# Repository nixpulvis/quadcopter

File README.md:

# Quadrocopter

 * __Nathan Lilienthal__ [@nixpulvis](https://github.com/nixpulvis)
 * __Alex Johnson__ [@alexjohnson505](https://github.com/alexjohnson505)

## Index

This project is comprised of a number of components. Below is a purpose and description for each main peice.

### gel

Gel is a simple OpenGL engine, created to assist in understanding and analyzing data through 3D visualization. One such part is the 3D representation of data provided via the IMU.

### serial_monitor

Serial monitor reads data from the Arduino by wrapping the `SerialPort` class from the `serialport` gem.

The Arduino application's serial monitor is good for human reading the output, but Serial Monitor allows additional programs to read the data.

### imu_visualization

IMU_visualization reads IMU data from the Arduino over serial, and creates 3D models of the data allowing us to create a visual 3D represenation of the captured data.

### smc

This program will sit on an Arduino acting as the quadcopter's SMC. It handles reading IMU data over I2C and performing the required math to accurately determinate valid pitch, roll, and yaw values. Based on it's knowledge of the quadcopters current inertial status, the SMC will drive the motors to the correct speed required to reach the calculated pitch, roll, yaw values.

## Tasks

We are maintaining the action items for this project on [Trello](https://trello.com/b/EygHwZfX).

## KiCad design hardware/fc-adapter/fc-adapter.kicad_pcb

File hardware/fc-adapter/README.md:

# FC adapter / power board (rev A)

A 94 × 94 mm, 2-layer, 1 oz copper, 1.6 mm FR4 board that bolts rigidly to the
frame's nylon standoffs. It carries the battery connector, the 4-way ESC power
bus, the ESC signal header, and plug-in ports for the receiver, GPS + Remote ID and PM02. It holds the Lumenier LUX F765 NDAA flight controller
(38 × 38 mm, 30.5 mm M3) on standoffs with rubber grommets.

```
  [      FC       ]   <- floats on 4x M3 rubber grommets
     |  |  |  |       <- M3 standoffs, ~10 mm, 30.5 mm square
  [  this board   ]   <- bolted rigidly to the frame standoffs
  [  frame plate  ]
```

| Top | Bottom (mirrored, as seen from below) |
|---|---|
|  |  |

Schematic: [docs/schematic.svg](docs/schematic.svg).
DRC: [docs/drc.rpt](docs/drc.rpt). Schematic/board net check: [docs/netlist-check.txt](docs/netlist-check.txt).

Rev A is the first board to be fabricated. Earlier unbuilt drafts targeted the
Matek H743-WING V3 and the CoreWing F405 WING V2, which both sold out. The LUX
has no power board or current sensor, so a Holybro PM02 sits between the
battery and this board.

## Power path

```
battery -> Holybro PM02 (current + voltage sense, cable to J9) -> J1 XT60
J1 -> ESC bus pours -> M1..M4 ESC pads
                    -> P1/P2 "FC VBAT" -> FC battery pads
```

Every power pad has a + or - mark beside it.

* **VBAT_ESC** is a near full-board pour on the top layer and **GND_ESC** on the
  bottom. Exposed copper strips beside the FC area can be loaded with solder.
* The PM02 measures all the current, motors and electronics alike, because
  everything downstream of it runs through this board.
* Signal ground (the front strip) only meets GND_ESC through the FC.
* C1 and C2 (1000 µF 35 V low-ESR each) sit across the ESC bus, one on each
  side, so the board stays balanced.
* Power pads connect solidly to the pours (no thermal reliefs), so use a big
  iron for the XT60 and wire pads.

## Signals and ports

| Ref | What | Pins |
|---|---|---|
| J2 | ESC servo plugs, 3 × 4 | rows S (signal), NC (ESC BEC 5V, not connected), G; columns S1–S4 |
| J3 | FC LINK | S1, S2, S3, S4, G |
| J5 / J6 | GPS+ID socket (JST-GH 6) / its FC lead pads | RX, TX, G, 5V, SCL, SDA |
| J7 / J8 | RX (receiver) socket (JST-GH 4) / its FC lead pads | 5V, TX, RX, G |
| J9 / J10 | PM02 socket (JST-GH 6) / its FC lead pads | socket: VCC, VCC (both NC), CUR, VOLT, G, G; pads: CUR, VOLT |

The ESC plugs fit unmodified: their red wire lands on the NC row, so the four
ESC BECs never feed the FC. J3 takes a short 5-wire lead to the FC's S1–S4 and
G pads.

The LUX has only solder pads, so every device plugs into this board instead.
Each port has a row of pads for a short lead soldered once to the FC, and a
JST-GH socket for the device:

* **GPS+ID (J5/J6)** is for the BeeID Pro M10, which does GPS, compass and Remote ID from one plug. The socket follows the BeeID Pro's
  listed order (ReadyMadeRC: TX, RX, GND, 5V, SCL, SDA, from the module's
  side), so the module's stock GH cable plugs straight in; the FC lead pads are
  labelled from the FC side (RX, TX, G, 5V, SCL, SDA). Wire J6 to one FC UART
  group plus SDA/SCL (the LUX has GND, 5V, RX3, TX3, SDA, SCL side by side).
  Check the pads printed on the module against this when it arrives.
* **RX (J7/J8)** is for the ELRS receiver. Wire J8 to another UART group (the
  LUX has TX8, RX8, 5V, GND together). The receiver's lead needs a JST-GH
  plug with its RX on the TX pin and its TX on the RX pin.
* **PM02 (J9/J10)**, at the rear by the XT60, takes the PM02's sense cable.
  Its 5V is left unconnected because the LUX has its own BEC, and its ground
  is the battery negative, which is already this board's ESC bus. So J10 only
  needs two wires: CUR to the FC's Curr pad, and optionally VOLT (the FC
  already reads the battery voltage on its VBAT pads).

The front ports all read the same way, front edge to back: the device's
connector, the pad row for the lead to the FC, the pin names, then the port's
name. The ESC header is turned so its G row is at the edge and its S row
faces the FC link.

TX and RX are named from the FC's side everywhere. Keep the receiver itself
on its lead, away from the copper pours, with the antenna out in the open.

Remote ID comes from the BeeID Pro M10 on the GPS+ID socket. NewBeeDrone's
FAA declaration RID000001995 (model "BeeID", accepted) covers serials
2071F000000000000000 to 2071FZZZZZZZZZZZZZZZ, so check the module's serial
starts with 2071F.

ArduPilot (target `LumenierLUXF765-NDAA`): motors are outputs 1–4
(`SERVOn_FUNCTION` 33–36), so J3 S1–S4 go to the FC's S1–S4.

Motor numbering follows ArduPilot Quad X: M1 front-right, M2 rear-left,
M3 front-left, M4 rear-right. Each ESC pad pair has two zip-tie slots for
strain relief.

## Still to confirm

* **Which LUX UARTs** go to J6 and J8. The silkscreen groups are read off
  photos; check them against the `LumenierLUXF765-NDAA` hwdef and set
  `SERIALn_PROTOCOL` (5 for GPS, 23 for RC) and `BATT_CURR_PIN` to match.
* **Frame standoffs** are 44 × 44 mm centre to centre, M3 (measured). They
  sit just outside the FC's corners, so the frame screw heads end up under
  the FC, which clears them on its ~10 mm standoffs. The nuts or screw ends
  of the FC standoffs hang under this board, so the frame standoffs must be
  taller than those.
* **Nothing taller than about 4 mm goes under the FC.** It sits about
  10 mm up on grommets and has parts on its underside, so the 54 mm square
  under it is kept for low parts only (it's empty).
* The XT60 is rated about 30 A continuous / 60 A burst. That covers hover and
  normal flight; `MOT_BAT_CURR_MAX ≈ 70` limits the peaks.

## Working on it

The KiCad files are the source of truth once you start editing in KiCad
(7.0 or newer). The scripts bootstrapped the board and are handy while the
mechanical numbers are still moving, but `generate.py` overwrites both files:

```sh
python3 scripts/generate.py   # schematic, placement, pours, the four S tracks
python3 scripts/check.py      # fill pours, DRC + schematic/board net check
scripts/export.sh             # renders (docs/) and Gerbers (fab/)
```

Use the Python that ships with KiCad (`python3.12` on Ubuntu 24.04's KiCad 7).
`scripts/route.py` (Freerouting) is only needed if signal nets come back that
`generate.py` doesn't route itself. `export.sh` writes `fab/fc-adapter-gerbers.zip`. Rev A is ordered as bare
boards from OSH Park's standard 2-layer service (1.6 mm, 1 oz, ENIG), with the
parts hand-soldered: the XT60 (J1), C1, C2 and the three GH sockets (J5, J7,
J9) besides the headers and wires. The power pours span the whole board, so
1 oz is enough; OSH Park's 2 oz service only comes as a 0.8 mm board, too
flexible for one that carries the FC.

### Ordering with assembly (JLCPCB, not used for rev A)

`export.sh` also writes `fab/jlcpcb-bom.csv` and `fab/jlcpcb-cpl.csv`. Upload
them with the Gerber zip and pick PCB Assembly. They list only the parts
JLCPCB fits: the XT60 (J1), C1, C2 and the three GH sockets (J5, J7, J9). The rest
(the ESC and FC LINK headers, wire pads and the FC lead pad rows) is soldered
by hand. Those parts are marked with `MPN`, `LCSC` and `JLCPCB` fields, which
are set in `ASSEMBLY` in `scripts/generate.py`.

* No LCSC numbers are filled in yet. JLCPCB's order page matches the part
  number and lets you pick a stocked part.
* Check every part's rotation in JLCPCB's placement preview before paying.

Project-local parts live in `lib/` (`fc-adapter.pretty`, `fc-adapter.kicad_sym`):
wire pads for 12/14AWG leads, the 3 × 4 ESC header and the zip-tie slot.
Everything else comes from KiCad's standard libraries.

KiCad 7's command line has no ERC, so `check.py` compares every pin's net in
the schematic netlist against the matching pad on the board instead.

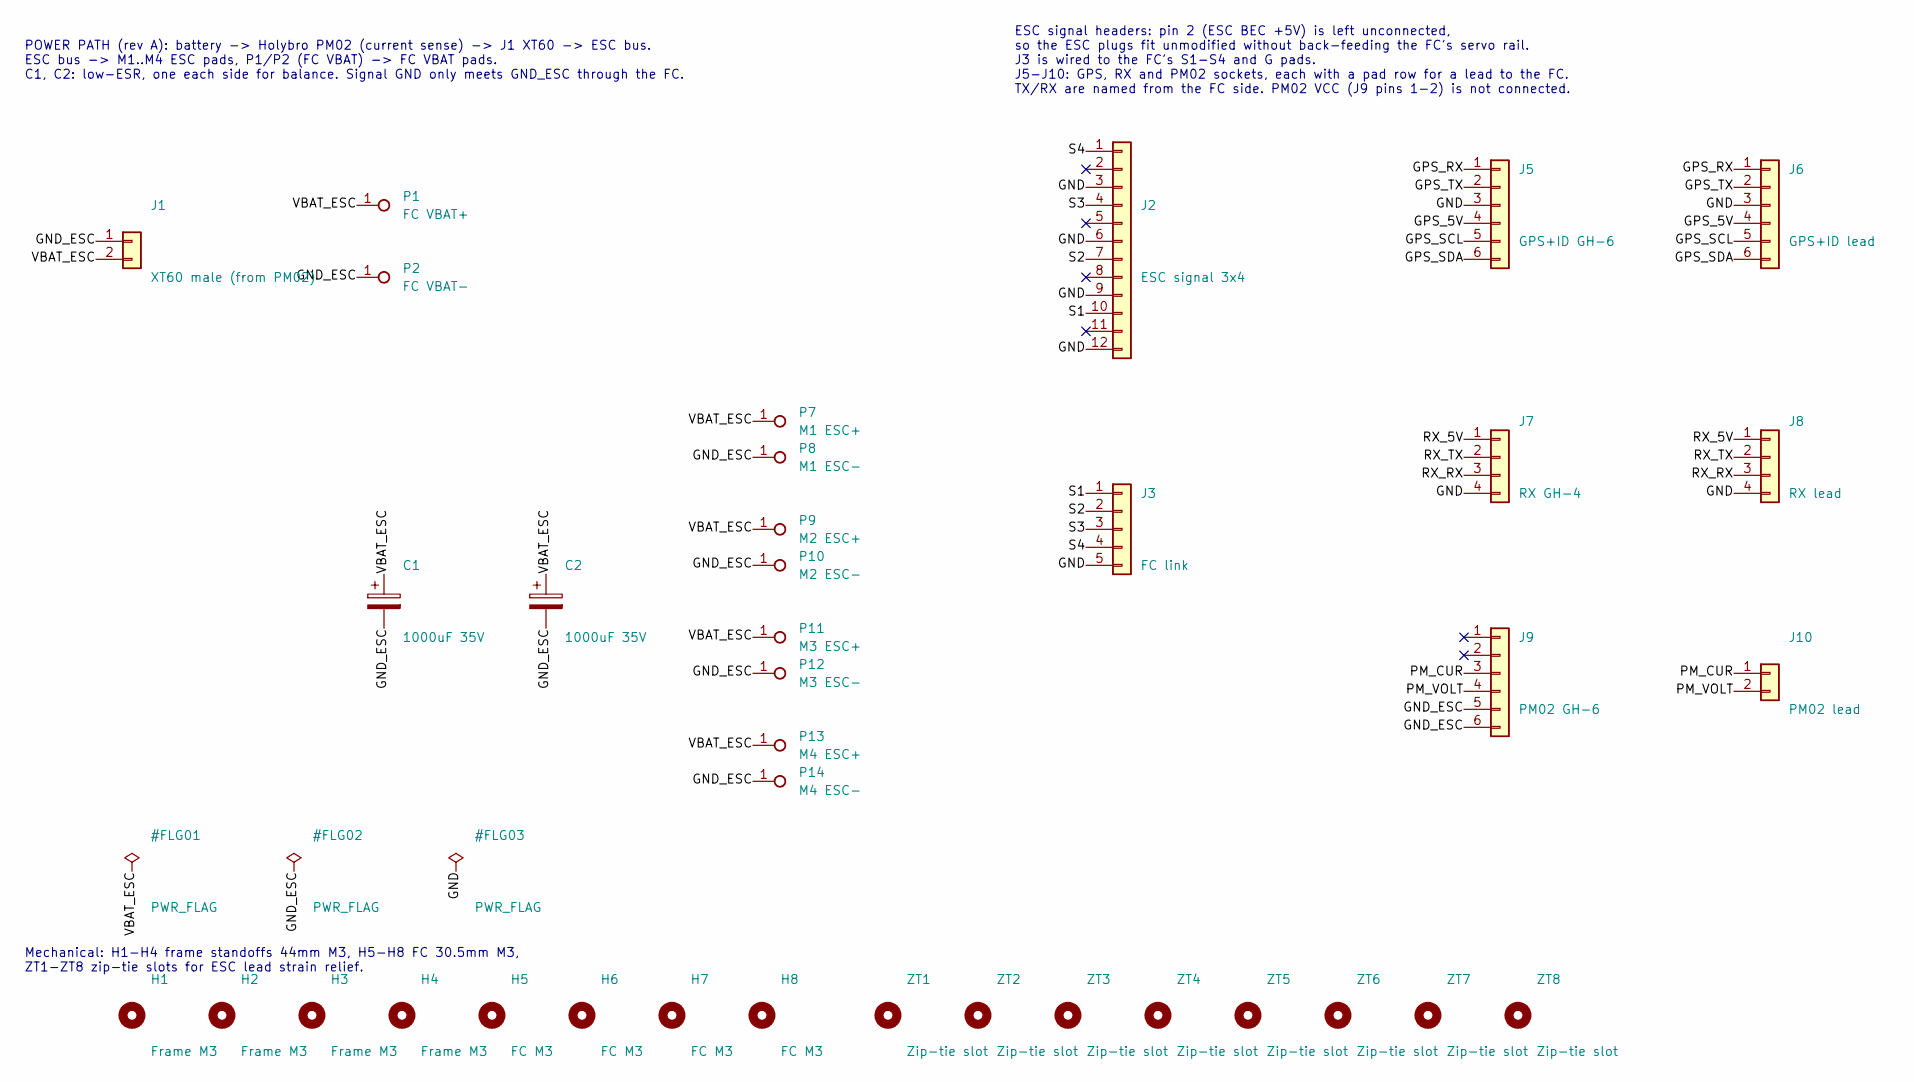
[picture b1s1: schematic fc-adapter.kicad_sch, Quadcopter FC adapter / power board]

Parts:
C1, C2: 1000uF 35V; CP_Radial_D12.5mm_P5.00mm; MPN 1000uF 35V low-ESR electrolytic, 12.5mm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; JLCPCB fit
H1, H2, H3, H4: Frame M3; MountingHole_3.2mm_M3
H5, H6, H7, H8: FC M3; MountingHole_3.2mm_M3
J1: XT60 male (from PM02); AMASS_XT60PW-M_1x02_P7.20mm_Horizontal; MPN Amass XT60PW-M; JLCPCB fit
J2: ESC signal 3x4; ESC_Header_3x04_P2.54mm
J3: FC link; PinHeader_1x05_P2.54mm_Vertical
J5: GPS+ID GH-6; JST_GH_BM06B-GHS-TBT_1x06-1MP_P1.25mm_Vertical; MPN JST BM06B-GHS-TBT; JLCPCB fit
J6: GPS+ID lead; PinHeader_1x06_P2.54mm_Vertical
J7: RX GH-4; JST_GH_BM04B-GHS-TBT_1x04-1MP_P1.25mm_Vertical; MPN JST BM04B-GHS-TBT; JLCPCB fit
J8: RX lead; PinHeader_1x04_P2.54mm_Vertical
J9: PM02 GH-6; JST_GH_BM06B-GHS-TBT_1x06-1MP_P1.25mm_Vertical; MPN JST BM06B-GHS-TBT; JLCPCB fit
J10: PM02 lead; PinHeader_1x02_P2.54mm_Vertical
P1: FC VBAT+; WirePad_14AWG
P2: FC VBAT-; WirePad_14AWG
P7: M1 ESC+; WirePad_14AWG
P8: M1 ESC-; WirePad_14AWG
P9: M2 ESC+; WirePad_14AWG
P10: M2 ESC-; WirePad_14AWG
P11: M3 ESC+; WirePad_14AWG
P12: M3 ESC-; WirePad_14AWG
P13: M4 ESC+; WirePad_14AWG
P14: M4 ESC-; WirePad_14AWG
ZT1, ZT2, ZT3, ZT4, ZT5, ZT6, ZT7, ZT8: Zip-tie slot; ZipTieSlot_1.6x4.0mm

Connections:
GND: J2.3, J2.6, J2.9, J2.12, J3.5, J5.3, J6.3, J7.4, J8.4
GND_ESC: C1.2, C2.2, J1.1, J9.5, J9.6, P2.1, P8.1, P10.1, P12.1, P14.1
GPS_5V: J5.4, J6.4
GPS_RX: J5.1, J6.1
GPS_SCL: J5.5, J6.5
GPS_SDA: J5.6, J6.6
GPS_TX: J5.2, J6.2
PM_CUR: J9.3, J10.1
PM_VOLT: J9.4, J10.2
RX_5V: J7.1, J8.1
RX_RX: J7.3, J8.3
RX_TX: J7.2, J8.2
S1: J2.10, J3.1
S2: J2.7, J3.2
S3: J2.4, J3.3
S4: J2.1, J3.4
VBAT_ESC: C1.1, C2.1, J1.2, P1.1, P7.1, P9.1, P11.1, P13.1

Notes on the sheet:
POWER PATH (rev A): battery -> Holybro PM02 (current sense) -> J1 XT60 -> ESC bus. ESC bus -> M1..M4 ESC pads, P1/P2 (FC VBAT) -> FC VBAT pads. C1, C2: low-ESR, one each side for balance. Signal GND only meets GND_ESC through the FC.
ESC signal headers: pin 2 (ESC BEC +5V) is left unconnected, so the ESC plugs fit unmodified without back-feeding the FC's servo rail. J3 is wired to the FC's S1-S4 and G pads. J5-J10: GPS, RX and PM02 sockets, each with a pad row for a lead to the FC. TX/RX are named from the FC side. PM02 VCC (J9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
Mechanical: H1-H4 frame standoffs 44mm M3, H5-H8 FC 30.5mm M3, ZT1-ZT8 zip-tie slots for ESC lead strain relief.

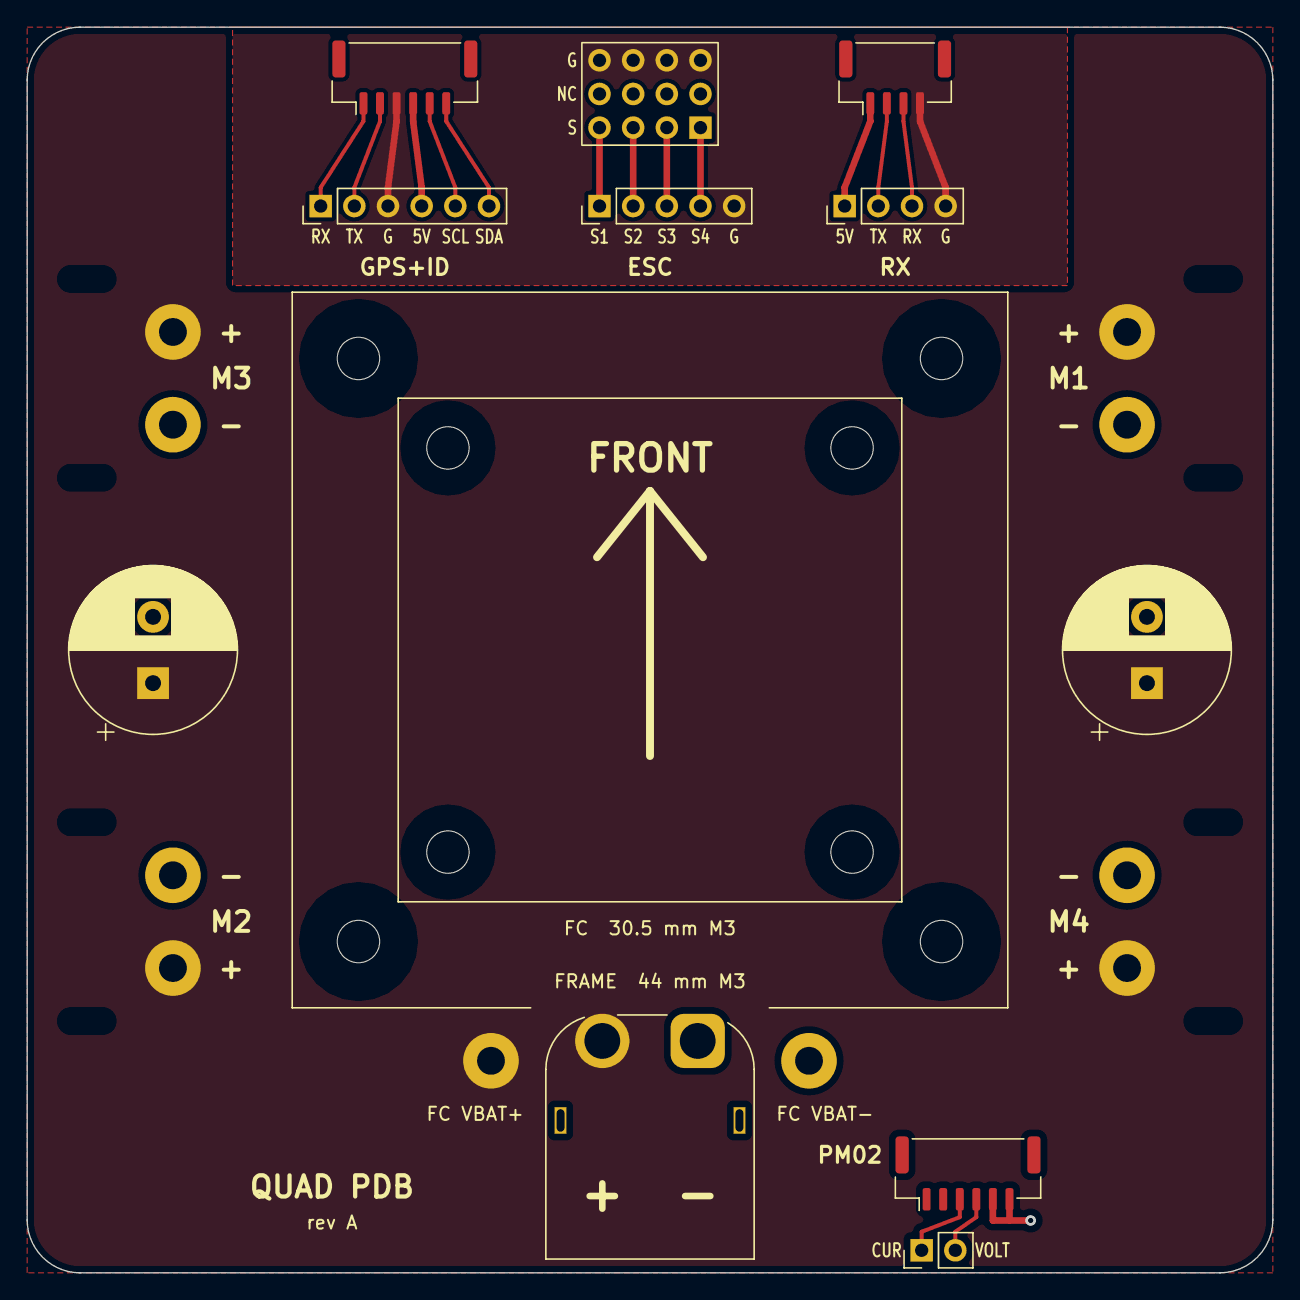
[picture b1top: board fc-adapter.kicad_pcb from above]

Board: 2 copper layers, 94.0 x 94.0 mm, 37 parts (0 on the bottom side), 17 nets.

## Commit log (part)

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2013-04-07 init
2013-04-07 add links
2013-04-07 Add more links
2013-04-09 starting parts list
2013-04-11 no checkboxes in README.md :(
2013-05-13 Adding some ESC/Motor control code.
2013-05-13 Simplification and comments.
2013-05-13 Removing parts list.
2013-05-13 Removing cruft from README.
2013-05-13 Adding some notes.
2013-05-21 Handle array of motors.
    All code in the Arduino.ino is basicly just for testing, not going to be
    of any use for actually flying anything.
2013-05-21 Apperently Serial.parseInt is a thing...
2013-05-22 More docs for the hardware.
2013-05-22 Fix broken link.
2013-05-22 Removing unused variable in smc.ino.
2013-05-22 Readme update with links to documentation.
2013-05-22 Renaming arduino code to be the start of the SMC.
    The Stable Motor Controller, or (SMC) is the arduino on-board in charge
    of stabilizing the flight of the arduino.
2013-05-22 Documentation belongs in doc/
2013-05-23 cleaned up readme, added links to some algorithm PDFS, began writing notes on stabilization and IMU conversions
2013-06-02 Added some kalman formulas and the beginning of the quadrocopter model.
2013-06-02 Fixing list items that start with latex
2013-06-02 Added expansion, attempts to fix list rendering. There will be many commits for now until I get local rendering working. Too late for it right now.
2013-06-02 typo
2013-06-02 another typo
2013-06-02 too many typos
2013-06-07 Beginning serial monitor.
    https://trello.com/c/w0dtCBVH
2013-06-07 Adding commandline argument for serialport.
2013-06-07 Command shold be serial-monitor.
2013-06-07 Adding the beginnings of the IMU visualization.
    With OpenGL we can somewhat easily draw 3D objects and move them around.
    We'll be making a box to represent the IMU for the quadcopter. Currently
    I have the box rotating on all 3 axises.
2013-06-07 IMU visualization's graphics engine moved to gem.
    Named Gel.
2013-06-07 Adding special key and loop support.
2013-06-07 Even better IMU representation. A CLASS!
2013-06-07 Remove color from boxes, and add normals.
2013-06-07 Adding lighting, and reset rotation.
2013-06-09 Test IMU Gyro data
    https://trello.com/c/MBalIj7P
    Beginning work on:
    Use Actual IMU Data in OpenGL IMU Visualization
2013-06-09 Suppressing UTF read errors.
2013-06-10 README update.
2013-06-10 Adding examples to gel.
2013-06-12 Abstracting a box object in gel, and cleaning things a bit.
2013-06-13 Add arguments to serial monitor.
    Calling serial monitor now requires that the user provide
    the port to monitor, as well as the baud rate
    Fixes #4
    Fixes #5
2013-06-13 Add basic readme.
2013-06-13 Provide proper code highlighting markdown
2013-06-13 SerialMonitor extends SerialPort.
    fixes #11
    By simply extending serialport we get all it's functionality. Then we
    simply override what we need. In this case, for now we just need to wait
    a short amount of time, and then flush the input stream.
2013-06-14 Fix variables, error feedback
2013-06-14 Re-introduce casting baud rate as an int
2013-06-18 Adding comments explaining iflush.
2013-06-23 Adding rotation to box, and new example for it.
2013-06-23 Fix wording in README
2013-06-23 Update docs readme. Add hardware documentation
2013-06-23 Format hardware
2013-06-23 Add accessories
2013-06-23 Cleanup readmes and hardware links
2013-06-28 Singular example.
2013-06-28 Starting the README.
2013-06-28 Adding mouse based hooks, and an input example.
2013-06-28 Updating example to match style of other.
2013-06-28 Set all colors easily with some faked shading.
2013-06-28 Only call set if it was defined.
2013-06-28 Finishing cleaning up IMU class.
2013-06-28 Beginning object oriented refactor.
2013-06-28 Update for compatibility with serial monitor.
2013-06-28 Update to use gel box.
2013-06-29 Units are determained and set properly.
2013-06-29 Updating imu visualization to use units properly.
    Integration of delta_x,y,z needs a notion of time. Once integrated the
    values will maintain thier units. Since the last commit got the arduino
    sending the gyro values in degrees/second, integrating these values
    leaves us with degrees. Perfect for OpenGL rendering.
2013-06-29 basic complementary filter code
2013-06-29 restoring Gemfile.lock for imu-visualization
2013-06-29 `update_rotation` uses the comp. filter.
    `update_rotation` should now use the `estimate_angle` function to apply
    our rudimentary complementary filter to the gyroscope and accelerometer data.
2013-07-01 Update logic for calculating position with accelerometer
2013-07-01 Adding a status light to the arduino code.
2013-07-01 Basic complementory filter. Z axis is fucked.
2013-07-01 Moving imu's component classes into a subfolder.
2013-07-01 Cleaning up Coordinate class with OpenStruct.
2013-07-01 IMU components should expose "pitch/roll/yaw" not x,y,z.
2013-07-04 REALLY REALLY AWESOME HACKY CODE INCLUDED! ARE YOU READY.
    fixes #9
2013-07-04 Majorly cleaned up. See new MPU lib.
    https://github.com/nixpulvis/MPU9150
2013-07-04 Remove left over comment.
2013-07-07 Removing old debug code.
2013-07-12 removing code to be added as submodules.
2013-07-12 Adding submodules.
2013-07-12 Fixing imu to work with renamed serial_communicator.
2013-07-16 Adding alex's docs repo to the project as a submodule.
2013-07-17 Moving axial_control back into the repo.
    This code will never be shared outside of the repo. Being a submodule
    was pointless.
2013-07-29 not sure why I missed this.
2013-07-29 Adding scaling for accel and gyro.
2013-07-29 Adding time delta calculations.
2013-07-30 Adding comments and some calculations.
2013-07-31 Account for gyro spinup.
2013-07-31 Get the scale from the MPU itself.
2013-08-04 PID / Kalman started.
2013-08-12 Adding changes done for live test run 1.
2013-08-12 Renaming serial.
2013-08-12 update the name of the git repo for docs.
2013-08-13 Use new (ruby-serialport less) serial impl.
2015-02-23 update submodules
2015-02-23 add mpu test shenanigans
2015-04-01 Adding the hardware spec WIP.
2015-08-26 Forgot to commit this.
2015-08-26 Skeleton esc proj.
2015-12-24 Cruft.
2016-09-28 Starting the rust project.
2016-10-16 Top level build
2016-10-16 Adding the blink work
2016-10-16 Don't want to commit object files.
2016-10-16 Updating the gitignore.
2016-11-29 Starting with clear rust.
2016-11-29 Update build to not use avr.
2016-11-30 Starting hardware descriptions.
2016-11-30 Remove old docs.
2016-12-01 Starting on the CLI.
